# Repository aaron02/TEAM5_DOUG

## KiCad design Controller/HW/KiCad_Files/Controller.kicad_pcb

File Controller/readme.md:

# Controller

## Links

Text to MP3: https://voicegenerator.io/

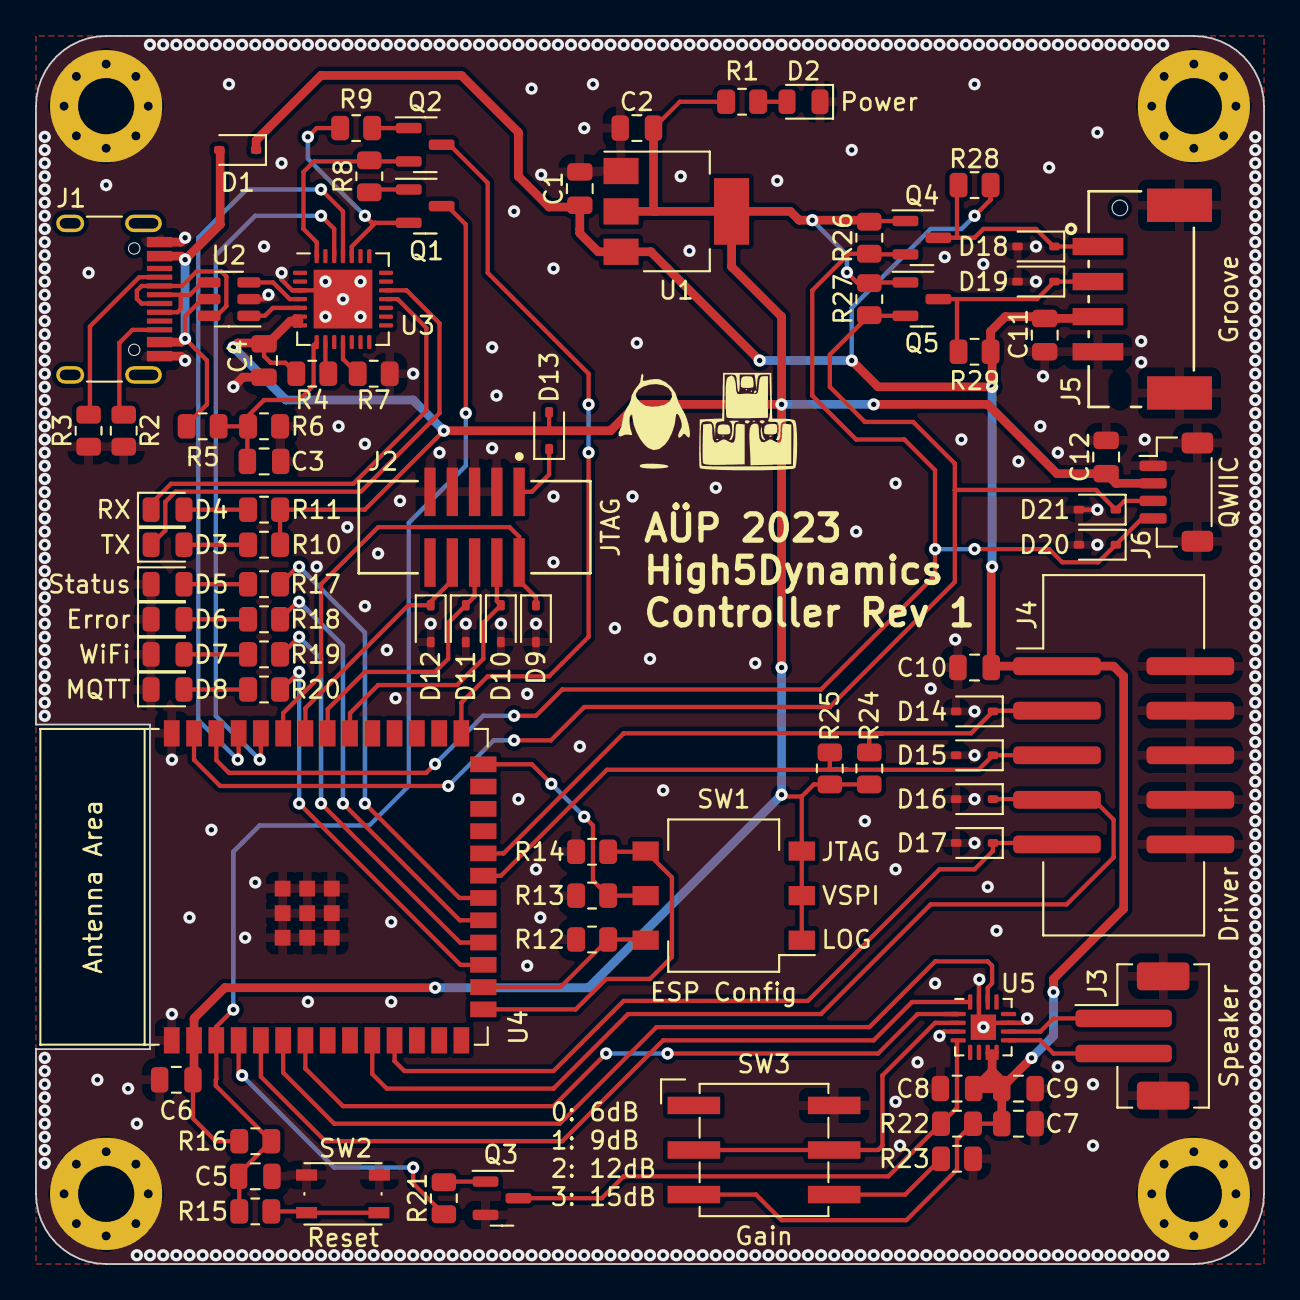
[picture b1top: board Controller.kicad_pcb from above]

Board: 4 copper layers, 70.0 x 70.0 mm, 85 parts (0 on the bottom side), 61 nets.

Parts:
C1, C2, C4, C6, C7: 10u; C_0805_2012Metric
C3, C8, C9, C10, C11, C12: 100n; C_0805_2012Metric
C5: 1u; C_0805_2012Metric
D1, D13: NSR0320; D_SOD-323
D2: Power; LED_0805_2012Metric
D3: TX; LED_0805_2012Metric
D4: RX; LED_0805_2012Metric
D5: Status; LED_0805_2012Metric
D6: Error; LED_0805_2012Metric
D7: WiFi; LED_0805_2012Metric
D8: MQTT; LED_0805_2012Metric
D9, D10, D11, D12, D14, D15, D16, D17, D18, D19, D20, D21: D1213A; D_SOD-323
H1, H2, H3, H4: M3; MountingHole_3.2mm_M3_Pad_Via
J1: USB; USB_C_Receptacle_HRO_TYPE-C-31-M-12
J2: JTAG; CNC_Tech-3220-10-0300-00-MFG
J3: Speaker; JST_PH_B2B-PH-SM4-TB_1x02-1MP_P2.00mm_Vertical
J4: Driver; IDC-Header_2x05_P2.54mm_Vertical_SMD
J5: Groove; CONN_BM04B-PASS-1-TFTLFSN_JST
J6: QWIIC; JST_SH_BM04B-SRSS-TB_1x04-1MP_P1.00mm_Vertical
Q1, Q2, Q3: MMBT3904; SOT-23
Q4, Q5: NX138AK; SOT-23
R1, R4, R10, R11, R15, R17, R18, R19, R20: 1k; R_0805_2012Metric
R2, R3: 5.1k; R_0805_2012Metric
R5: 22.1k; R_0805_2012Metric
R6: 47.5k; R_0805_2012Metric
R7, R8, R9, R12, R13, R14, R16, R21, R22, R24, R25, R26, R27, R28, R29: 10k; R_0805_2012Metric
R23: 100k; R_0805_2012Metric
SW1: ESP Config; SW_DIP_SPSTx03_Slide_Omron_A6S-310x_W8.9mm_P2.54mm
SW2: Reset; SW_Push_1P1T_NO_Vertical_Wuerth_434133025816
SW3: Gain; Nidec_Copal_SH-7010B
U1: AP1117-33; SOT-223-3_TabPin2
U2: USBLC6-2SC6; SOT-23-6
U3: CP2102N-Axx-xQFN28; QFN-28-1EP_5x5mm_P0.5mm_EP3.35x3.35mm
U4: ESP32-S3-WROOM-1
U5: MAX98357A; QFN-16-1EP_3x3mm_P0.5mm_EP1.45x1.45mm

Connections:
+3.3V: C2.2, C4.2, C6.1, C12.2, D13.2 (A), J6.2, Q4.1 (G), Q5.1 (G), R1.1, R4.1, R10.1, R11.1, R16.1, R24.1, R25.1, R26.1, R27.1, SW1.1, SW1.2, SW1.3, U1.2 (VO), U3.6 (VDD), U3.7 (VREGIN), U4.2 (3V3)
+5V: C1.2, C7.1, C8.1, C9.1, C10.2, C11.2, D1.1 (K), J4.1, J5.3, R22.1, R28.1, R29.1, SW3.0 (D0), U1.3 (VI), U5.7 (VDD), U5.8 (VDD)
/Audio/Amp_Shutdown: R21.1, U4.4 (GPIO4/TOUCH4/ADC1_CH3)
/Audio/BCLK: U4.5 (GPIO5/TOUCH5/ADC1_CH4), U5.16 (BCLK)
/Audio/DIN: U4.7 (GPIO7/TOUCH7/ADC1_CH6), U5.1 (DIN)
/Audio/LRCLK: U4.6 (GPIO6/TOUCH6/ADC1_CH5), U5.14 (LRCLK)
/ESP32/Boot: Q2.3 (C), U4.27 (GPIO0/BOOT)
/ESP32/Controller_Interrupt: D14.1 (A1), J4.3, R24.2, U4.22 (GPIO14/TOUCH14/ADC2_CH3/FSPIWP/FSPIDQS/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)
/ESP32/Driver_Interrupt: D15.1 (A1), J4.5, R25.2, U4.21 (GPIO13/TOUCH13/ADC2_CH2/FSPIQ/FSPIIO7/S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)
/ESP32/JTAG: R14.1, SW1.4, U4.15 (GPIO3/TOUCH3/ADC1_CH2)
/ESP32/LOG: R12.1, SW1.6, U4.16 (GPIO46)
/ESP32/PRG_RX: U3.26 (TXD), U4.36 (U0RXD/GPIO44/CLK_OUT2)
/ESP32/PRG_TX: U3.25 (RXD), U4.37 (U0TXD/GPIO43/CLK_OUT1)
/ESP32/RX_Driver: D17.1 (A1), J4.9, U4.11 (GPIO18/U1RXD/ADC2_CH7/CLK_OUT3)
/ESP32/Rst: C5.1, Q1.3 (C), R15.2, R16.2, U4.3 (EN)
/ESP32/SCL: D20.1 (A1), J6.4, Q4.2 (S), R26.2, U4.38 (GPIO2/TOUCH2/ADC1_CH1)
/ESP32/SDA: D21.1 (A1), J6.3, Q5.2 (S), R27.2, U4.39 (GPIO1/TOUCH1/ADC1_CH0)
/ESP32/TCK: D10.1 (A1), J2.4, U4.32 (MTCK/GPIO39/CLK_OUT3/SUBSPICS1)
/ESP32/TDI: D12.1 (A1), J2.8, U4.34 (MTDI/GPIO41/CLK_OUT1)
/ESP32/TDO: D11.1 (A1), J2.6, U4.33 (MTDO/GPIO40/CLK_OUT2)
/ESP32/TMS: D9.1 (A1), J2.2, U4.35 (MTMS/GPIO42)
/ESP32/TX_Driver: D16.1 (A1), J4.7, U4.10 (GPIO17/U1TXD/ADC2_CH6)
/ESP32/VSPI: R13.1, SW1.5, U4.26 (GPIO45)
/USB Programmer/D+: U2.3 (I/O2), U3.4 (D+)
/USB Programmer/D+_USB: J1.A6 (D+), J1.B6 (D+), U2.4 (I/O3)
/USB Programmer/D-: U2.1 (I/O1), U3.5 (D-)
/USB Programmer/D-_USB: J1.A7 (D-), J1.B7 (D-), U2.6 (I/O4)
/USB Programmer/PRG_DTR: Q2.2 (E), R8.1, U3.28 (~DTR)
/USB Programmer/PRG_RTS: Q1.2 (E), R9.1, U3.24 (~RTS)
GND: C1.1, C2.1, C3.2, C4.1, C5.2, C6.2, C7.2, C8.2, C9.2, C10.1, C11.1, C12.1, D2.1 (K), D5.1 (K), D6.1 (K), D7.1 (K), D8.1 (K), D9.2 (A2), D10.2 (A2), D11.2 (A2), D12.2 (A2), D14.2 (A2), D15.2 (A2), D16.2 (A2), D17.2 (A2), D18.2 (A2), D19.2 (A2), D20.2 (A2), D21.2 (A2), H1.1, H2.1, H3.1, H4.1, J1.A1 (GND), J1.A12 (GND), J1.B1 (GND), J1.B12 (GND), J2.3, J2.5, J2.7, J2.9, J3.MP, J4.2, J4.4, J4.6, J4.8, J4.10, J5.4, J5.MP, J6.1, J6.MP, Q3.2 (E), R2.2, R3.2, R6.2, R7.2, R12.2, R13.2, R14.2, R23.2, SW2.1, SW3.2 (D2), U1.1 (GND), U2.2 (GND), U3.3 (GND), U3.29 (PAD), U4.1 (GND), U4.40 (GND), U4.41 (PAD), U5.3 (GND), U5.11 (GND), U5.15 (GND), U5.17 (PAD)
unnamed: D2.2 (A), R1.2
unnamed: D3.2 (A), R10.2
unnamed: D3.1 (K), U3.19 (~TXT/GPIO.0)
unnamed: D4.2 (A), R11.2
unnamed: D4.1 (K), U3.18 (~RXT/GPIO.1)
unnamed: D5.2 (A), R17.2
unnamed: D6.2 (A), R18.2
unnamed: D7.2 (A), R19.2
unnamed: D8.2 (A), R20.2
unnamed: D13.1 (K), J2.1
unnamed: D18.1 (A1), J5.1, Q4.3 (D), R28.2
unnamed: D19.1 (A1), J5.2, Q5.3 (D), R29.2
unnamed: J1.A5 (CC1), R3.1
unnamed: J1.B5 (CC2), R2.1
unnamed: J3.1, U5.10 (OUTN)
unnamed: J3.2, U5.9 (OUTP)
unnamed: Q1.1 (B), R8.2
unnamed: Q2.1 (B), R9.2
unnamed: Q3.1 (B), R21.2
unnamed: Q3.3 (C), R22.2, U5.4 (~SD_MODE)
unnamed: R15.1, SW2.2
unnamed: SW3.C (CM), U5.2 (GAIN_SLOT)
unnamed: R23.1, SW3.3 (D3)
unnamed: C3.1, R5.2, R6.1, U3.8 (VBUS)
unnamed: R4.2, U3.9 (~RST)
unnamed: R7.1, U3.11 (~SUSPEND)
unnamed: R20.1, U4.17 (GPIO9/TOUCH9/ADC1_CH8/FSPIHD/SUBSPIHD)
unnamed: R19.1, U4.18 (GPIO10/TOUCH10/ADC1_CH9/FSPICS0/FSPIIO4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)
unnamed: R18.1, U4.19 (GPIO11/TOUCH11/ADC2_CH0/FSPID/FSPIIO5/S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)
unnamed: R17.1, U4.20 (GPIO12/TOUCH12/ADC2_CH1/FSPICLK/FSPIIO6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)
VBUS: D1.2 (A), J1.A4 (VBUS), J1.A9 (VBUS), J1.B4 (VBUS), J1.B9 (VBUS), R5.1, U2.5 (VBUS)

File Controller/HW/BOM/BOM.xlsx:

Reference | Value | DigiKey | Qty
J1 | USB |  | 1
SW2 | Reset |  | 1
J4 | Driver | 1175-1621-ND | 1
J2 | JTAG | 1175-1629-ND | 1
C5 | 1u | 1276-1026-1-ND | 1
C1, C2, C4, C6, C7 | 10u | 1276-1096-1-ND | 5
C3, C8-C12 | 100n | 1276-2449-1-ND | 6
Q4, Q5 | NX138AK | 1727-2731-1-ND | 2
Q1-Q3 | MMBT3904 | 1727-4044-1-ND | 3
U4 | ESP32-S3-WROOM-1 | 1965-ESP32-S3-WROOM-1-N8CT-ND | 1
SW1 | ESP Config | 2223-DS04-254-2-03BK-SMT-ND | 1
R6 | 47.5k | 311-47.5KCRCT-ND | 1
U3 | CP2102N-Axx-xQFN28 | 336-5890-1-ND | 1
J6 | QWIIC | 455-1790-1-ND | 1
J5 | Groove | 455-2639-1-ND | 1
J3 | Speaker | 455-2872-1-ND | 1
D6 | Error | 475-1278-1-ND | 1
D3 | TX | 475-1410-1-ND | 1
D4 | RX | 475-1410-1-ND | 1
D5 | Status | 475-1410-1-ND | 1
D7 | WiFi | 475-1410-1-ND | 1
D8 | MQTT | 475-1410-1-ND | 1
D2 | Power | 475-2488-1-ND | 1
U2 | USBLC6-2SC6 | 497-5235-1-ND | 1
SW3 | Gain | 563-1217-1-ND | 1
U1 | AP1117-33 | AZ1117IH-3.3TRG1DICT-ND | 1
R1, R4, R10, R11, R15, R17-R20 | 1k | CR0805-FX-1001ELFCT-ND | 9
R7-R9, R12-R14, R16, R21, R22, R24-R29 | 10k | CR0805-FX-1002ELFCT-ND | 15
R23 | 100k | CR0805-FX-1003ELFCT-ND | 1
R5 | 22.1k | CR0805-FX-2212ELFCT-ND | 1
R2, R3 | 5.1k | CR0805-FX-5101ELFCT-ND | 2
D9-D12, D14-D21 | D1213A | D1213A-01WS-7DICT-ND | 12
U5 | MAX98357A | MAX98357AETE+TCT-ND | 1
D1, D13 | NSR0320 | NSR0320MW2T3GOSCT-ND | 2

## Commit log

2023-04-11 Initial Project
2023-04-20 Odimetry Korrektur und Board auf Teensy geändert.
2023-04-20 Falsche Datei Geladen..
2023-04-22 Programmanpassung für neue IO Pins, Multirthrearding Libary um Motoren in einer Seperaten Loop laufen zu lassen
2023-04-22 Added Power Distributiuon Board for Voltage and Current Sensing
2023-04-27 KiCad Projekt hinzugefügt
2023-04-27 moved gitignore for KiCad
2023-04-27 remove files using KiCad gitignore file
2023-04-29 korrektur der Odometry und Gyro vorrübergehend ausgeschaltet.
2023-04-29 PCB Zwischenstand
2023-04-30 Controller Rev 1 PCB fertig
2023-04-30 BOM update
2023-05-01 fotos
2023-05-06 Korrektur der Strommessung
2023-05-06 Created KiCad Project for driver
2023-05-06 zwischenstand
2023-05-07 Driver Schema komplettiert
2023-05-07 Schemas aktualisiert mit PDF
2023-05-07 Programm Korrektur und Testfahrt akitiviert
2023-05-07 platformio projekt erstellt
2023-05-07 blink
2023-05-07 multitasking Beispiel
2023-05-07 Test Drive X
2023-05-07 Ordner verschoben
2023-05-07 Gitignore verschoben
2023-05-10 Gyro Programmierung korrigiert zu BNO 085 Debug variabeln hinzugefügt
2023-05-11 Aufteilung des Programmes, Gyro korrekt eingebunden
2023-05-13 Korrektur des Sensoroffsets
2023-05-20 Schrittmotor Drehen eingebunden, Programm Optimiert
2023-05-22 test
2023-05-25 work in progress
2023-05-25 antrieb_V2
2023-05-26 Neuer Schrittmotor Code
2023-05-26 Greiffer Programm
    Greifer.h und Greifer.cpp erstellt und mit Basisfunktionen gespickt
2023-05-27 set drive speeds to a good value
2023-05-27 Json Test1
2023-05-27 Funktion bei Greifer Hinzugefügt
    Grundstellung Funktion erstellt. Wird immer beim Aufrufen des Greifer.h ausgeführt. Bei Greifer.h diverse Positionen definiert.
2023-05-27 Kommunikation getestet und funktionstüchtig
2023-05-28 Fahren nach Position eingebunden und Compilierfehler ausgemertzt
2023-05-28 positionsfenster eingebunden 0 kann warscheinlich nicht erreicht werden
2023-05-28 Korrektur POsition reached und Communications angepasst
2023-05-28 Communications GetPOsition
2023-05-28 Prüfe Länge um Waypoint Fehler zu vermeiden
2023-05-28 füge greiffer in main loop ein
2023-05-28 some comments
2023-05-28 Power Board Limit Battery pct to 100
2023-05-28 implement a proper Opcode soloution
2023-05-28 implement updateable class
2023-05-28 organize our files
2023-05-28 Korrektur drehrichtung
2023-05-28 PickPackage and inposition
    inposition erstelllt. PickPackage angefangen.
2023-05-28 GS angepasst
    Sollte so nun die Komplette Schrittkette durchlaufen.
2023-05-28 GS angepasst Klammer vergessen
    Klammer vergessen
2023-05-28 Diverse Hinzugefügt
    mit Aaron
2023-05-29 fix compile issue
2023-05-29 Programm Optimierungen im Absoluten Fahrbetrieb
2023-05-29 ReadMotion Timed Test
2023-05-29 auf mm geändert
2023-05-29 schickt etwas über serial nach mqtt befehl
2023-05-30 kosmetik
2023-05-30 lauft getestet mit aaron
2023-05-30 Kommunikation getestet mit Lorenz
2023-06-01 Place and Pick Package
    Sind fertig, nur Abstandssensor zur genauen Position anfahren fehlt. Müssten wir noch mit der Funktion mNavigation->setSollPosition(); kombinieren
2023-06-01 PlacePackage case 202 falscher Name
    richtigen namen gegeben
2023-06-02 Greiffer Angepasst
2023-06-02 Roboter Automatisch drehen damit die Fahrtrichtung der Grössten Distanz Entspricht
2023-06-02 IBN Rotation ausstehend
2023-06-02 Kommunikation und Greiffer Angeppast
    mit Aaron änderungen vorgenommen
2023-06-03 IBN Robotersteuerung mit Lorin, Fabian
2023-06-04 kommunikation erweitert
2023-06-04 gyro kommunikation angepasst
2023-06-04 Kommunikation Debug
2023-06-04 experimental
2023-06-05 Roboter zu Ziel Drehen Optimiert
2023-06-08 Controller ready für IBN
2023-06-08 korrektur roboter
2023-06-09 Testcode für IBN mit Robo
2023-06-10 Schema Angepasst
2023-06-11 Kommunikation neu Organisiert
2023-06-12 Updated PDF
2023-06-12 PDF aktualisiert
2023-06-15 compiles!!
2023-06-15 ready for testing
2023-06-15 format
2023-06-15 I2C mit M5Stack
    Library macht noch Probleme
2023-06-16 Beim aufstarten auf Roboter warten. Data/Autonom bei place package mitschicken
2023-06-16 Include backup order
2023-06-17 TOF-Sensor und Hub eingebunden Distanzwerte werden ausgegeben und sind Korrekt
2023-06-17 Korrektur funktion
2023-06-18 Arm state wird beim init robot abgefragt
2023-06-18 fixed includes Log.h
2023-06-18 improved updates to MQTT
2023-06-18 Funktion zur berechnung der Startposition
2023-06-18 korrektur kommunikation
2023-06-18 audio funktioniert, RFID dummy code
2023-06-19 Maussensor neu kalibriert und mindestgeschwindigkeiten angepasst
2023-06-22 Drive, Geschwindigkeit und Toleranzen angepasst
2023-06-22 Fixes nach IBN
2023-06-25 schalter zum übernehmen der position eingebunden
2023-06-25 neuer navigationstreiber testweise aufgeschaltet
2023-06-25 gyro runden
2023-06-27 Fehlerhandling verbessert
2023-06-27 remove unused variables
2023-06-27 Audio File angepasst
